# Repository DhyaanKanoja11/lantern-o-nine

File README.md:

# **Lantern-o-Nine**

A 9-key custom macropad built around the Seeed XIAO RP2040, featuring an EC11 rotary encoder for volume control, a 0.91" OLED display to show current status, and SK6812 RGB underglow. Housed in a custom 3D printed snap-fit case with a honeycomb vent rosette and debossed name!

Made as a submission to [Hack Club's Hackpad](https://hackpad.hackclub.com/) program.  
> *This is my first hardware project! Thank you Hack Club for this amazing opportunity!! <3*

---

### Quick Links
- [View CAD Files](./CAD/)
- [View PCB Files](./PCB/)
- [View Firmware](./Firmware/)
- [View Production Files](./production/)

---

## Pictures & Design Files

### 3D PCB Renders
| Top View | Bottom View |
| :---: | :---: |
|  |  |

### Schematic & PCB Routing
| Schematic Diagram | 2D PCB Layout |
| :---: | :---: |
|  |  |

### 3D CAD Enclosure & Mechanical Assembly
| Exploded Assembly (PCB Encasing) | Fully Assembled Case | Bottom Case (Rosette & Logo) |
| :---: | :---: | :---: |
|  |  |  |

The 2-piece enclosure consists of a 6.0mm top plate and 9.2mm bottom shell:
- **Mechanical Encasing:** The custom 2-layer PCB (1.6mm FR4) drops directly into the bottom shell, seating flush on an internal perimeter retention shelf with dedicated clearance below for diode and switch pin solder joints.
- **Top Plate Retention:** The top plate caps the assembly, clamping the PCB securely while exposing the 9 Cherry MX switch stems through 14x14mm cutouts, an OLED viewing bezel, and a rotary encoder shaft opening.
- **Thermal & Ports:** The underside features an integrated 7-hex honeycomb ventilation rosette and debossed "Lantern-o-Nine" branding, with an aligned rear cutout for the Seeed Xiao USB-C port.

---

## Features
- **9 Cherry MX Mechanical Switches** in a 3x3 matrix with 1N4148 diodes so there's zero ghosting (NKRO).
- **EC11 Rotary Encoder** to smoothly change volume up/down, plus click-to-mute.
- **0.91" 128x32 I2C OLED Display** showing the active layer and status.
- **2x SK6812MINI-E Reverse-Mount RGB LEDs** shining through cutouts in the PCB for nice underglow.
- **Custom 3D Printed Case** with a 2mm switch plate, recessed PCB mounting ledge, USB-C cutout, debossed "Lantern-o-Nine" logo, and a little honeycomb vent pattern on the bottom!

---

## Components Used (BOM)

All parts are beginner friendly and follow the Hack Club approved parts list:

- **Seeed Studio XIAO RP2040** (1x)
- **Cherry MX / Gateron switches** (9x)
- **1N4148 switching diodes (DO-35)** (9x)
- **EC11 rotary encoder with push button** (1x)
- **0.91 inch SSD1306 I2C OLED display (128x32)** (1x)
- **SK6812MINI-E reverse-mount addressable RGB LEDs** (2x)
- **0805 SMD 0.1uF decoupling capacitors** (2x)
- **3D printed top plate and bottom case** (Printed in PLA/PETG)

---

## Xiao RP2040 Pinout

| Pin | GPIO | What it connects to |
| :--- | :--- | :--- |
| **D0** | GPIO26 | Encoder Pin B |
| **D1** | GPIO27 | Encoder Pin A |
| **D2** | GPIO28 | Matrix Row 1 (Diodes D1, D2, D3) |
| **D3** | GPIO29 | Matrix Row 2 (Diodes D4, D5, D6) |
| **D4** | GPIO6  | OLED Display SDA (I2C) |
| **D5** | GPIO7  | OLED Display SCL (I2C) |
| **D6** | GPIO0  | Matrix Row 3 (Diodes D7, D8, D9) |
| **D7** | GPIO1  | Matrix Column 1 (Switches SW2, SW5, SW8) |
| **D8** | GPIO2  | Matrix Column 2 (Switches SW3, SW6, SW9) |
| **D9** | GPIO4  | Matrix Column 3 (Switches SW4, SW7, SW10) |
| **D10**| GPIO3  | RGB LED Data Line (DIN) |
| **3V3**| 3.3V   | Power to OLED Display |
| **5V** | 5.0V   | Power to SK6812 RGB LEDs |
| **GND**| GND    | Ground Plane |

---

## Firmware (CircuitPython + KMK)

The firmware is super simple and runs using [KMK](https://github.com/KMKfw/kmk_firmware) on CircuitPython.

### How to set it up:
1. Hold the `BOOT` button on the Xiao RP2040 while plugging it into your computer with a USB-C cable.
2. Drag and drop the CircuitPython `.uf2` file for Xiao RP2040 from [circuitpython.org](https://circuitpython.org/board/seeed_xiao_rp2040/).
3. Once the drive reboots as `CIRCUITPY`, download [KMK Firmware](https://github.com/KMKfw/kmk_firmware) and copy the `kmk/` folder into the `CIRCUITPY` drive.
4. Copy [`Firmware/main.py`](./Firmware/main.py) into the `CIRCUITPY` drive and rename it to `code.py`.

### 3-Mode Layout:
- **Top Row (Mode Switchers):** Key 1 = Spotify Mode | Key 2 = Git Mode | Key 3 = Code Mode
- **Mode 1 (Spotify):** Prev Track, Play/Pause, Next Track, Vol Down, Mute, Vol Up
- **Mode 2 (Git):** `git status`, `git add .`, `git commit`, `git push`, Toggle Terminal (`Ctrl+~`), Clear (`Ctrl+L`)
- **Mode 3 (Code):** Copy (`Ctrl+C`), Paste (`Ctrl+V`), Cut (`Ctrl+X`), Undo (`Ctrl+Z`), Redo (`Ctrl+Y`), Format (`Shift+Alt+F`)
- **Rotary Knob:** Turn clockwise for Volume Up, counter-clockwise for Volume Down.

---

## Repository Structure

```text
lantern-o-nine/
├── README.md                 # This file!
├── .gitignore                # KiCad gitignore
├── CAD/
│   ├── assembled-model.STEP  # Full 3D assembly of case + PCB
│   ├── Top.STEP              # Switch plate CAD model
│   └── Bottom.STEP           # Bottom enclosure CAD model
├── PCB/
│   ├── hackpadtrial.kicad_pro# KiCad 10 project file
│   ├── hackpadtrial.kicad_sch# Schematic
│   ├── hackpadtrial.kicad_pcb# PCB Layout (96mm x 99.5mm, 2-layer, 0 DRC errors)
│   └── hackpadtrial.kicad_prl# KiCad settings
├── Firmware/
│   └── main.py               # CircuitPython & KMK keyboard code
├── production/
│   ├── gerbers.zip           # Gerbers and drill files for JLCPCB
│   ├── Top.STEP              # Switch plate 3D file
│   ├── Bottom.STEP           # Bottom case 3D file
│   └── main.py               # Production firmware copy
└── images/
    ├── render_iso.png
    ├── render_top.png
    ├── render_bottom.png
    ├── cad_exploded_view.png # Exploded view showing PCB encasing
    ├── cad_assembled_view.png# Fully assembled 3D case
    ├── cad_bottom_view.png   # Bottom shell with honeycomb & logo
    ├── schematic.svg
    └── pcb_layout.svg
```

---

## AI Declaration

AI tools (Antigravity CLI and ChatGPT) were used as educational mentors and engineering copilots throughout this build:
- **Mentorship & Tooling:** Learning new software workflows across KiCad 10, design rules, and CAD export standards.
- **Firmware Architecture:** Advice and guidance on structuring the 3-mode KMK keymap, matrix scanning, and CircuitPython extensions.
- **Documentation:** Assistance reviewing and structuring the README and project devlogs.

All circuit schematics, board routing, mechanical 3D tolerances, and component choices were designed and tested by me.

---

## Credits

Built by **Dhyaan Kanoja** ([@DhyaanKanoja11](https://github.com/DhyaanKanoja11)).  
Special thanks to **Atulya** ([@Person-0](https://github.com/Person-0)) for help and inspiration from his awesome [Spicofy](https://github.com/Person-0/spicofy) project!  
Huge shoutout to the **Hack Club** team and everyone on the Slack helping high schoolers build real hardware! <3

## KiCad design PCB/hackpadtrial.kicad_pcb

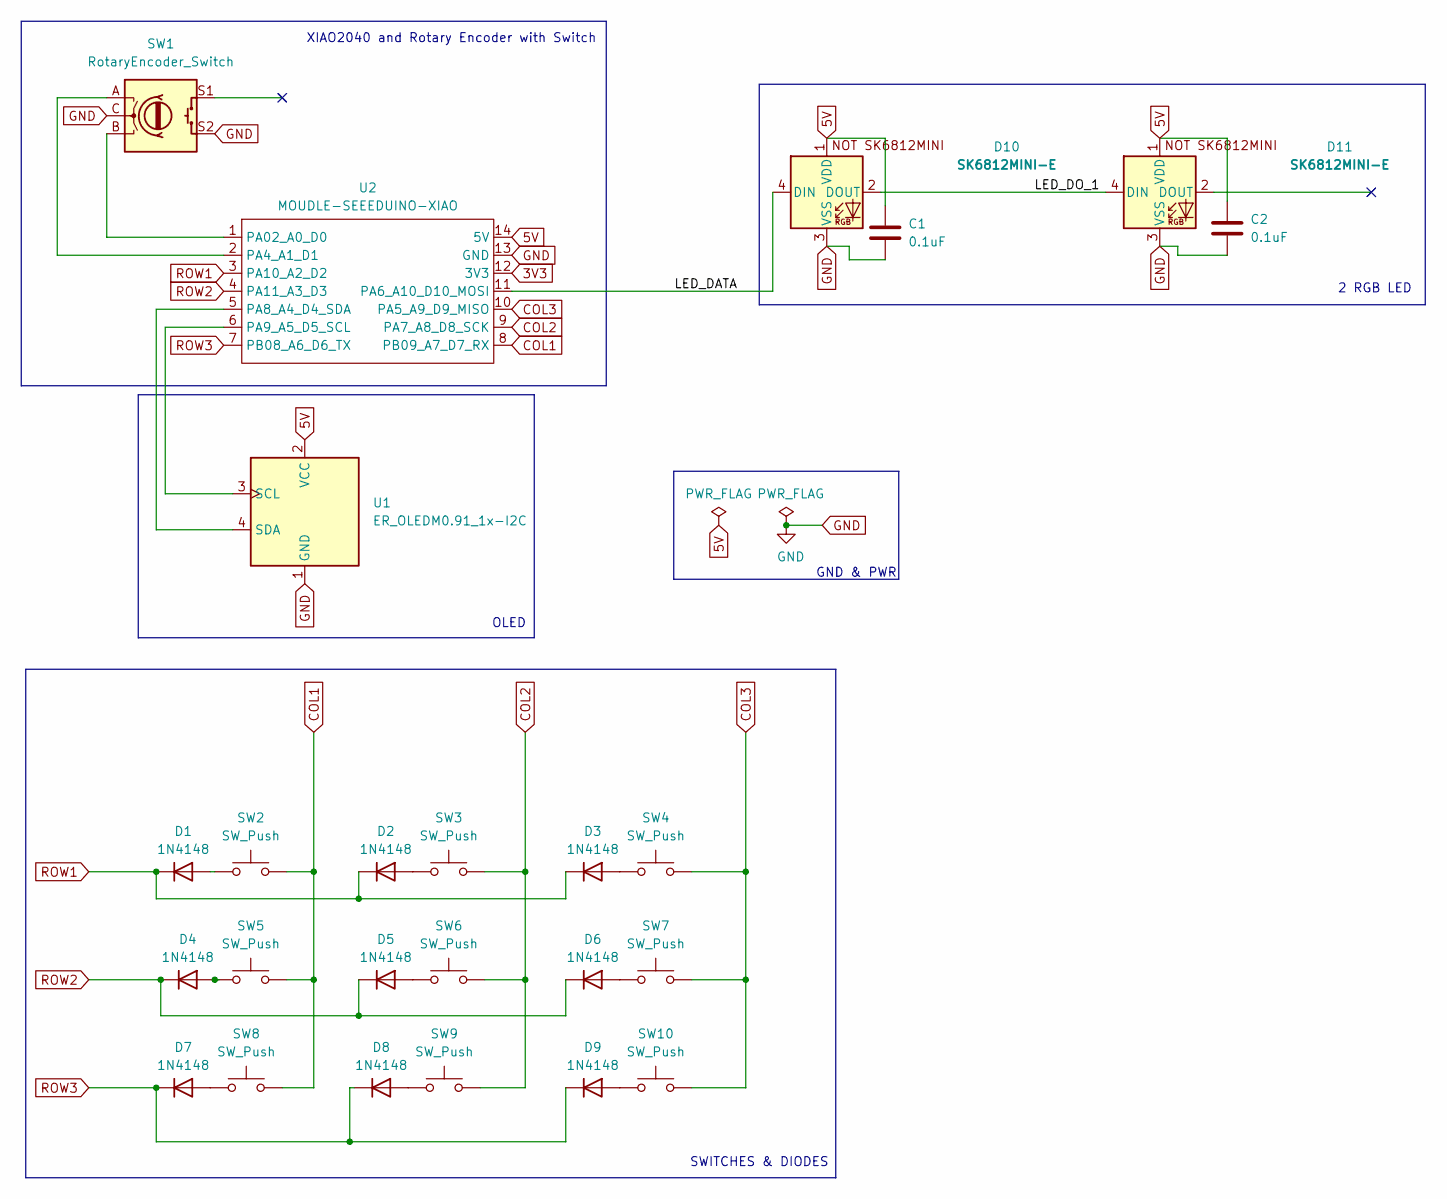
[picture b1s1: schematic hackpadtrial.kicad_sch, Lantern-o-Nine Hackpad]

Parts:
C1, C2: 0.1uF; C_0805_2012Metric_Pad1.18x1.45mm_HandSolder
D1, D2, D3, D4, D5, D6, D7, D8, D9: 1N4148; D_DO-35_SOD27_P7.62mm_Horizontal
D10, D11: SK6812MINI-E; SK6812MINI-E_fixed
SW1: RotaryEncoder_Switch; RotaryEncoder_Alps_EC11E-Switch_Vertical_H20mm
SW2, SW3, SW4, SW5, SW6, SW7, SW8, SW9, SW10: SW_Push; SW_Cherry_MX_1.00u_PCB
U1: ER_OLEDM0.91_1x-I2C
U2: MOUDLE-SEEEDUINO-XIAO; XIAO-Generic-Hybrid-14P-2.54-21X17.8MM

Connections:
3V3: U2.12 (3V3)
5V: C1.1, C2.1, D10.1 (VDD), D11.1 (VDD), U1.2 (VCC), U2.14 (5V)
/LED_DATA: D10.4 (DIN), U2.11 (PA6_A10_D10_MOSI)
/LED_DO_1: D10.2 (DOUT), D11.4 (DIN)
COL1: SW2.2, SW5.2, SW8.2, U2.8 (PB09_A7_D7_RX)
COL2: SW3.2, SW6.2, SW9.2, U2.9 (PA7_A8_D8_SCK)
COL3: SW4.2, SW7.2, SW10.2, U2.10 (PA5_A9_D9_MISO)
GND: C1.2, C2.2, D10.3 (VSS), D11.3 (VSS), SW1.C, SW1.S2, U1.1 (GND), U2.13 (GND)
unnamed: D1.2 (A), SW2.1
unnamed: D2.2 (A), SW3.1
unnamed: D3.2 (A), SW4.1
unnamed: D4.2 (A), SW5.1
unnamed: D5.2 (A), SW6.1
unnamed: D6.2 (A), SW7.1
unnamed: D7.2 (A), SW8.1
unnamed: D8.2 (A), SW9.1
unnamed: D9.2 (A), SW10.1
unnamed: U1.3 (SCL), U2.6 (PA9_A5_D5_SCL)
unnamed: U1.4 (SDA), U2.5 (PA8_A4_D4_SDA)
unnamed: SW1.B, U2.1 (PA02_A0_D0)
unnamed: SW1.A, U2.2 (PA4_A1_D1)
ROW1: D1.1 (K), D2.1 (K), D3.1 (K), U2.3 (PA10_A2_D2)
ROW2: D4.1 (K), D5.1 (K), D6.1 (K), U2.4 (PA11_A3_D3)
ROW3: D7.1 (K), D8.1 (K), D9.1 (K), U2.7 (PB08_A6_D6_TX)

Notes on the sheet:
2 RGB LED
GND & PWR
SWITCHES & DIODES
OLED
XIAO2040 and Rotary Encoder with Switch

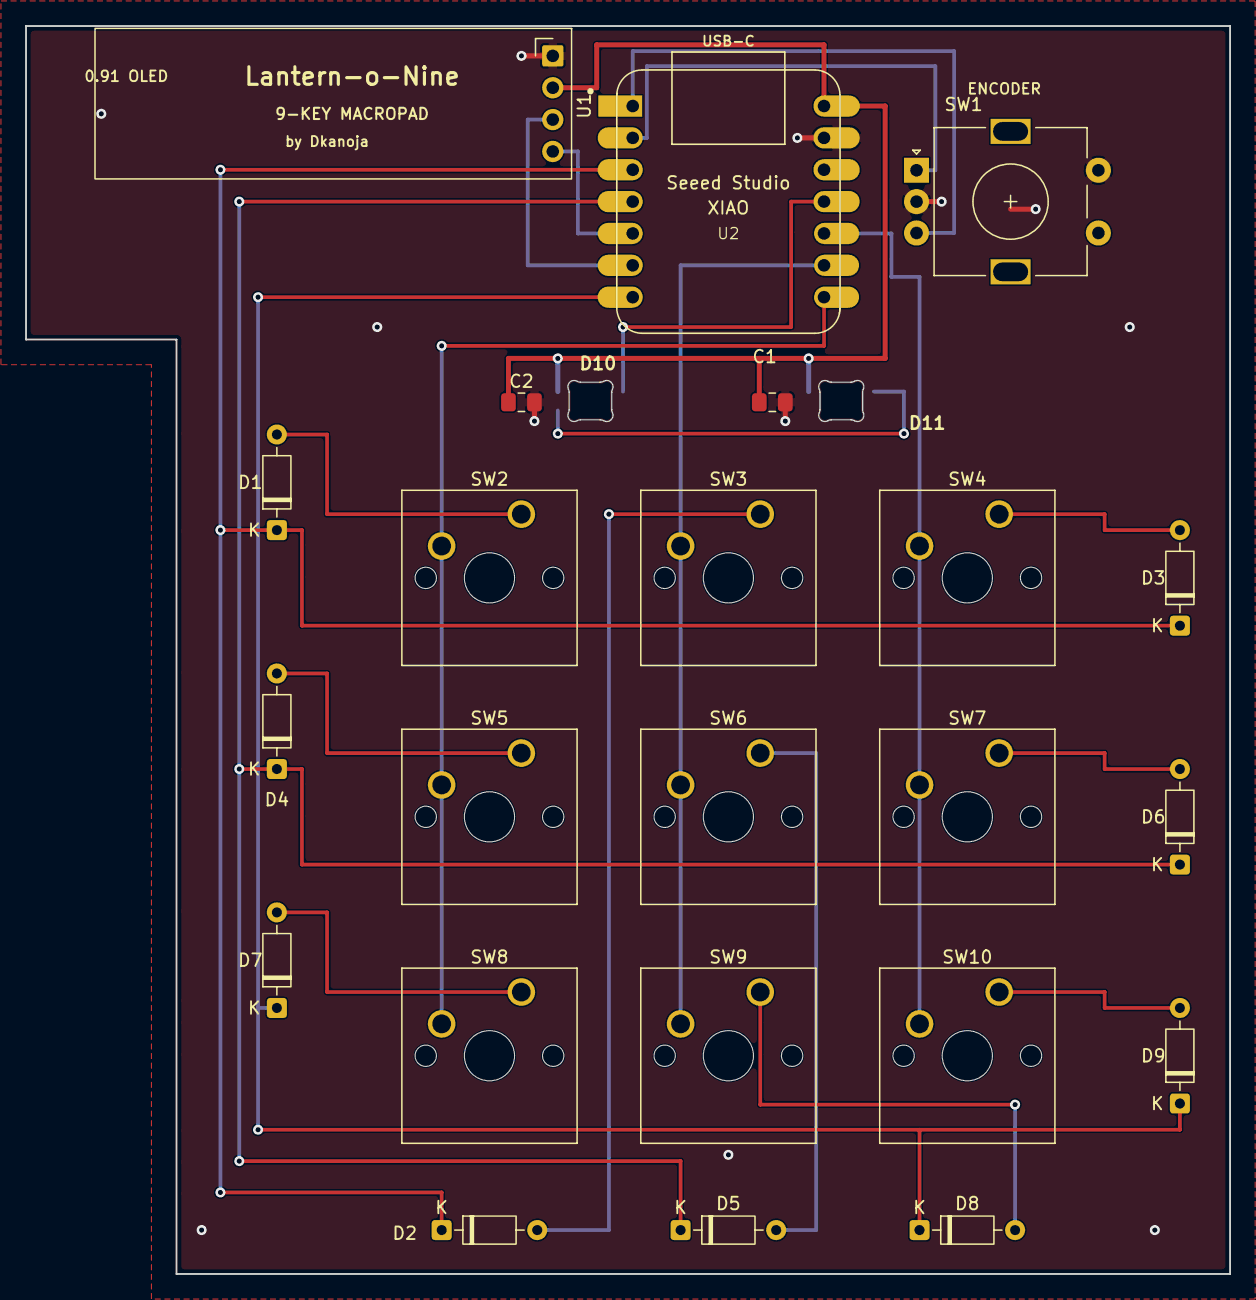
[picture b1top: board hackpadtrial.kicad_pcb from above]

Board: 2 copper layers, 96.0 x 99.5 mm, 25 parts (0 on the bottom side), 23 nets.
